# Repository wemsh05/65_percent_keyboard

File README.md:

# My first Keyboard design

This 65% keyboard is the first time I designed a pcb of my own and safe to say that I am really proud of it. The reason that I started with a keyboard is that my first mechanical keyboard used the classic ANSI layout. While usable, an idea popped in my head: what if I make my own keyboard that has 4 keys to the left of the space bar just like the laptop keyboards, and here I am.  

---

# Project Overview

This project is a two-layer FR4 board with hot-swappable cherry MX keys realized with kalih's hot swap sockets. It features an on-board usb c 2.0 port with ESD. Its MCU is the ATMega32U4 and it features an AVR 6-pin ISP connector to program the MCU firmware. The board also has a reset button and copper-grounded mounting holes. 

This project is inspired by MasterZen's 65% keyboard tutorial. But there are major differences as I did not simply copy his design. First, his designed utilized soldered ALPS footprints that in my opinion has more space for the routing and therefore slightly easier to route. The kalih hot swap sockets caused a barrier that traces can't be wired through the sockets unlike the tutorial and that took some time to get used to. Since this is my first time doing this, I also have not mastered the art of routing so the vias are probably more than the same project done by someone more skilled. 

---

# Schematic

The following is the overall keyboard schematic, which doesn't deviate too much from the tutorial. Although it seems that power flags have changed from the older kicad version the tutorial was using to kicad 10. 

The ESD protection device that I have on here is the PRTR5V0U2X, a device suitable for doing ESD protection for USB 2.0 devices. This was chosen because of ease of use and that it has a small package size. 

The AVR 6-pin ISP pin is added to flash the initial usb bootloader for future firmware uploads, it also provides a backup to not fully rely on the usb port for firmware uploads as bad firmware could render it useless. 

The grounded mounting hole pads are there because initially my plan is to eventually make an aluminum enclosure for it and these copper mounting hole pads could help with grounding. But in the event of a plastic or resin enclosure, the board would still not be in danger because of its existing grounding and ESD protection. 

---

# PCB layout

My first layout finished with a lot of vias, a lot of which isn't really necessary on the hotswap pads themselves. But I would say that there are definitely more vias than I would like on the MCU pads and near the MCU. 

Regarding the grounding, my friend who does pcbs much more than me says that usually he fills both sides that have no traces with copper but Masterzen said that I don't need to cover both sides with copper as ground as that could amplify cross-talk. He mentioned that 4 layer boards and above have their dedicated ground layers so it wouldn't be an issue for them. 

---

# Silkscreen and 3D effects

Currently, the silkscreen remains a free-hand drawing of what I imagine the final prototype to be as I don't have time to improve it. 

But on the front of 3d effects, I did end up choosing red as the final board color since I wanted the color to stand out a bit more but the official purple color is too muted. 

---

# Manufactured pictures

(Update on 8/19/2026)
The keyboard is now fully manufactured and I did have to end up choosing a matte light black since the manufacturer didn't have purple. But it did also turn out that the color was nice. For my first ever pcb project, the overall size definitely had the potential for optimization, but I believe overall this was a successful project. 

The front side 

The back side

---

# Firmware download success

I had to write the key matrix firmware for this board. Fortunately, the bootloader was already in the MCU which I somehow thought it wasn't. Currently I don't have the keys themselves to test multi-key rollover, but single keys do work:

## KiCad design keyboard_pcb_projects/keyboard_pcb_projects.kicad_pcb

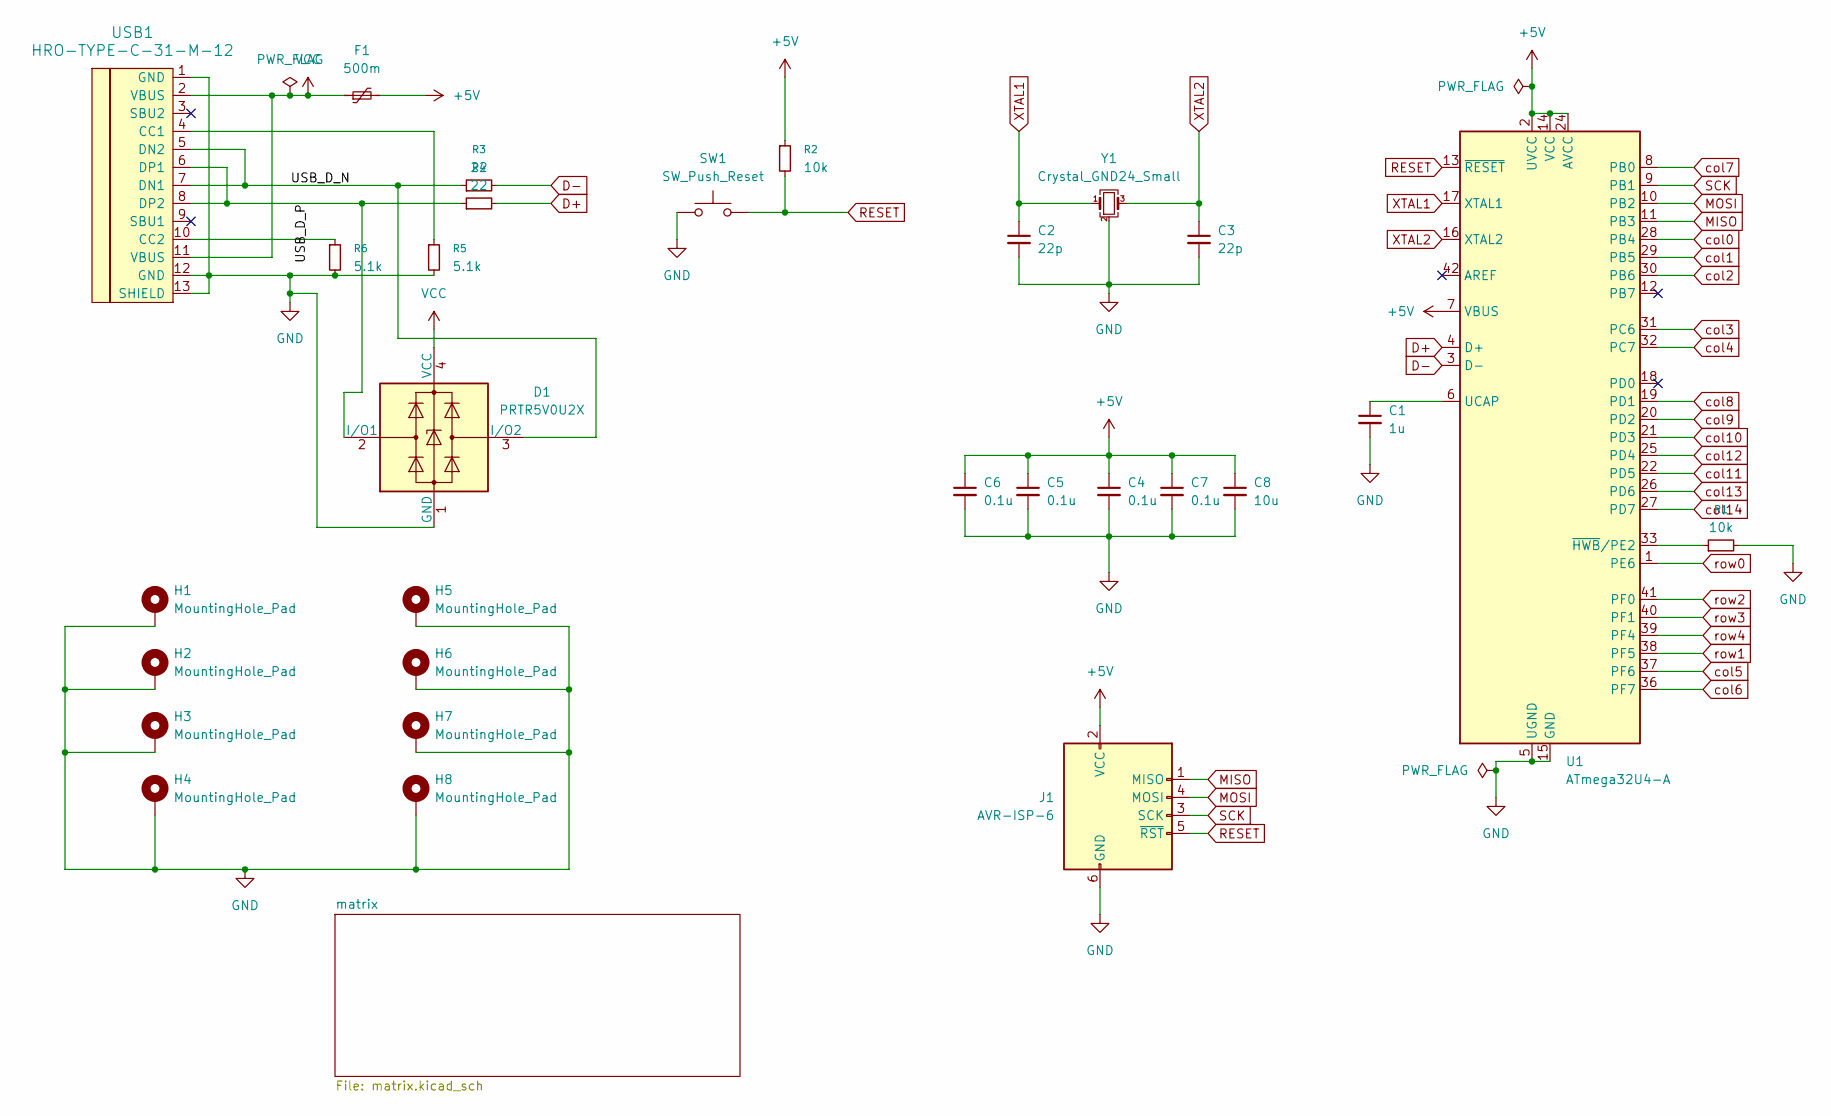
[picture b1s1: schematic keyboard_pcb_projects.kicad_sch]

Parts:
C1: 1u; C_0805_2012Metric_Pad1.18x1.45mm_HandSolder
C2, C3: 22p; C_0805_2012Metric_Pad1.18x1.45mm_HandSolder
C4, C5, C6, C7: 0.1u; C_0805_2012Metric_Pad1.18x1.45mm_HandSolder
C8: 10u; C_0805_2012Metric_Pad1.18x1.45mm_HandSolder
D1: PRTR5V0U2X; SOT-143
F1: 500m; Fuse_1206_3216Metric_Pad1.42x1.75mm_HandSolder
H1, H2, H3, H4, H5, H6, H7, H8: MountingHole_Pad; MountingHole_2.2mm_M2_Pad
J1: AVR-ISP-6; PinHeader_2x03_P2.54mm_Vertical
R1, R2: 10k; R_0805_2012Metric_Pad1.20x1.40mm_HandSolder
R3, R4: 22; R_0805_2012Metric_Pad1.20x1.40mm_HandSolder
R5, R6: 5.1k; R_0805_2012Metric_Pad1.20x1.40mm_HandSolder
SW1: SW_Push_Reset; SW_SPST_SKQG_WithStem
U1: ATmega32U4-A; TQFP-44_10x10mm_P0.8mm
USB1: HRO-TYPE-C-31-M-12; HRO-TYPE-C-31-M-12-HandSoldering
Y1: Crystal_GND24_Small; Crystal_SMD_3225-4Pin_3.2x2.5mm_HandSoldering

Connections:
+5V: C4.1, C5.1, C6.1, C7.1, C8.1, F1.2, J1.2 (VCC), R2.1, U1.2 (UVCC), U1.7 (VBUS), U1.14 (VCC), U1.24 (AVCC), U1.34 (VCC), U1.44 (AVCC)
/USB_D_N: D1.3 (I/O2), R3.1, USB1.5 (DN2), USB1.7 (DN1)
/USB_D_P: D1.2 (I/O1), R4.1, USB1.6 (DP1), USB1.8 (DP2)
D+: R4.2, U1.4 (D+)
D-: R3.2, U1.3 (D-)
GND: C1.2, C2.2, C3.2, C4.2, C5.2, C6.2, C7.2, C8.2, D1.1 (GND), H1.1 (1_1), H2.1 (1_1), H3.1 (1_1), H4.1 (1_1), H5.1 (1_1), H6.1 (1_1), H7.1 (1_1), H8.1 (1_1), J1.6 (GND), R1.2, R5.2, R6.2, SW1.1, U1.5 (UGND), U1.15 (GND), U1.23 (GND), U1.35 (GND), U1.43 (GND), USB1.1 (GND), USB1.12 (GND), USB1.13 (SHIELD), Y1.2 (G), Y1.4 (G)
MISO: J1.1 (MISO), U1.11 (PB3)
MOSI: J1.4 (MOSI), U1.10 (PB2)
unnamed: C1.1, U1.6 (UCAP)
unnamed: R1.1, U1.33 (~HWB/PE2)
unnamed: R5.1, USB1.4 (CC1)
unnamed: R6.1, USB1.10 (CC2)
RESET: J1.5 (~RST), R2.2, SW1.2, U1.13 (~RESET)
SCK: J1.3 (SCK), U1.9 (PB1)
VCC: D1.4 (VCC), F1.1, USB1.2 (VBUS), USB1.11 (VBUS)
XTAL1: C2.1, U1.17 (XTAL1), Y1.1
XTAL2: C3.1, U1.16 (XTAL2), Y1.3
col0: U1.28 (PB4); also elsewhere on the board
col1: U1.29 (PB5); also elsewhere on the board
col2: U1.30 (PB6); also elsewhere on the board
col3: U1.31 (PC6); also elsewhere on the board
col4: U1.32 (PC7); also elsewhere on the board
col5: U1.37 (PF6); also elsewhere on the board
col6: U1.36 (PF7); also elsewhere on the board
col7: U1.8 (PB0); also elsewhere on the board
col8: U1.19 (PD1); also elsewhere on the board
col9: U1.20 (PD2); also elsewhere on the board
col10: U1.21 (PD3); also elsewhere on the board
col11: U1.22 (PD5); also elsewhere on the board
col12: U1.25 (PD4); also elsewhere on the board
col13: U1.26 (PD6); also elsewhere on the board
col14: U1.27 (PD7); also elsewhere on the board
row0: U1.1 (PE6); also elsewhere on the board
row1: U1.38 (PF5); also elsewhere on the board
row2: U1.41 (PF0); also elsewhere on the board
row3: U1.40 (PF1); also elsewhere on the board
row4: U1.39 (PF4); also elsewhere on the board

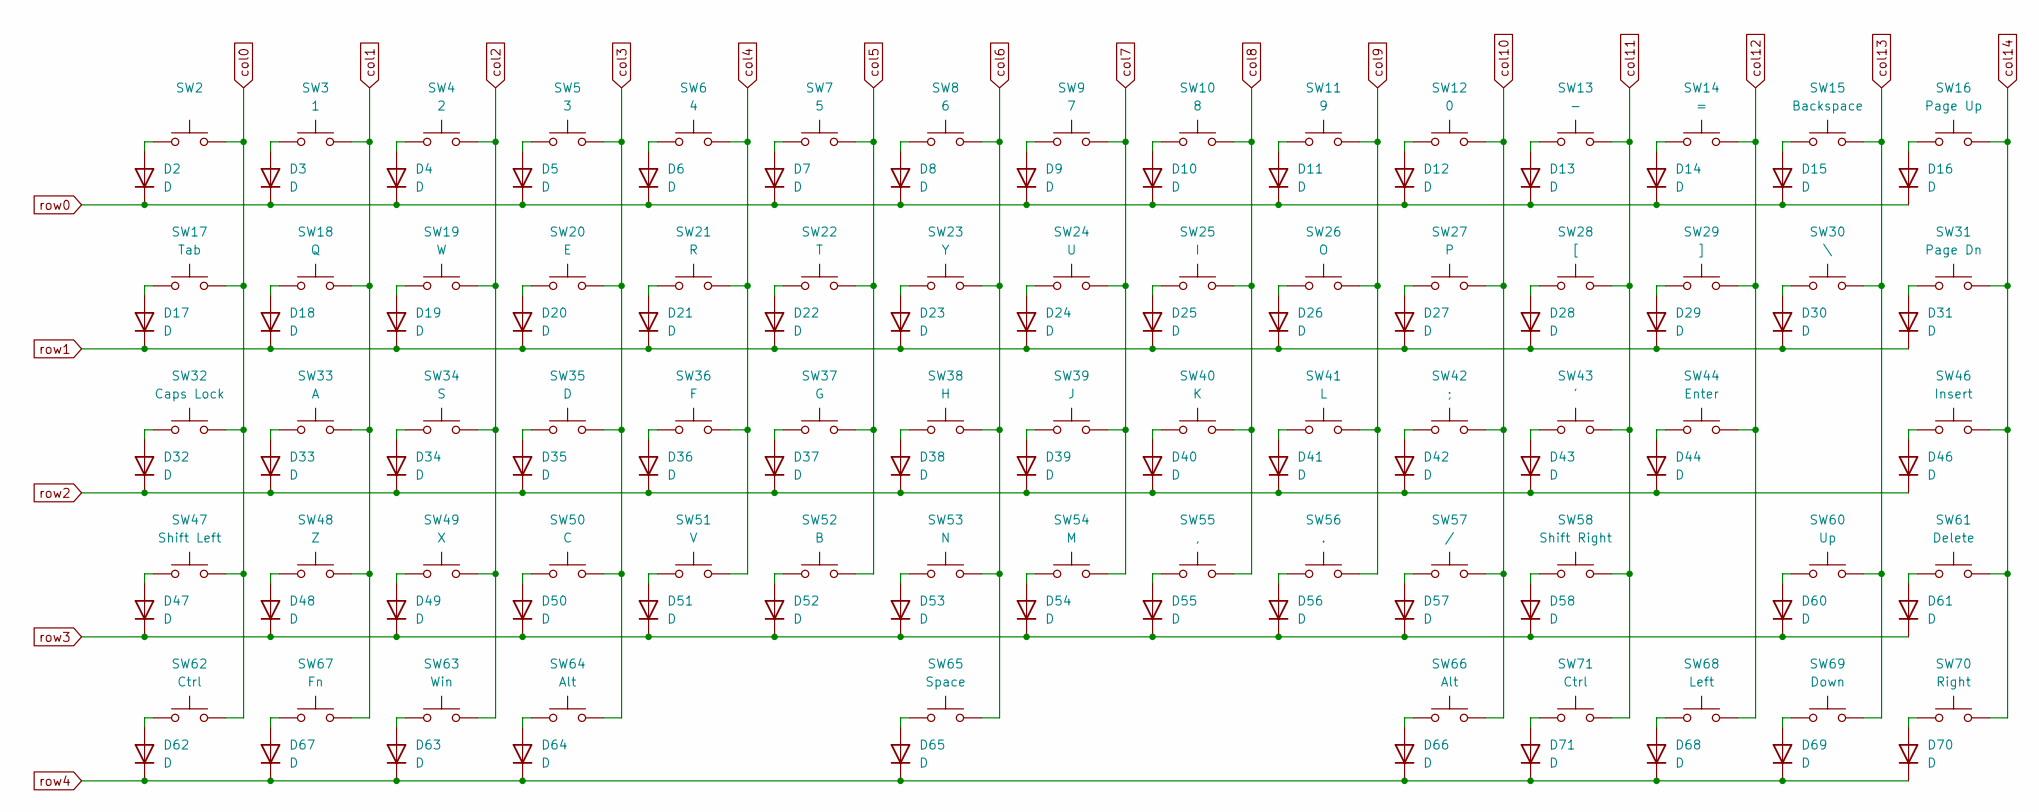
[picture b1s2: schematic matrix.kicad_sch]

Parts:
D2, D3, D4, D5, D6, D7, D8, D9, D10, D11, D12, D13, D14, D15, D16, D17, D18, D19, D20, D21, D22, D23, D24, D25, D26, D27, D28, D29, D30, D31, D32, D33, D34, D35, D36, D37, D38, D39, D40, D41, D42, D43, D44, D46, D47, D48, D49, D50, D51, D52, D53, D54, D55, D56, D57, D58, D60, D61, D62, D63, D64, D65, D66, D67, D68, D69, D70, D71: D; D_SOD-123
SW2: MX-Hotswap-1U
SW3: 1; MX-Hotswap-1U
SW4: 2; MX-Hotswap-1U
SW5: 3; MX-Hotswap-1U
SW6: 4; MX-Hotswap-1U
SW7: 5; MX-Hotswap-1U
SW8: 6; MX-Hotswap-1U
SW9: 7; MX-Hotswap-1U
SW10: 8; MX-Hotswap-1U
SW11: 9; MX-Hotswap-1U
SW12: 0; MX-Hotswap-1U
SW13: -; MX-Hotswap-1U
SW14: =; MX-Hotswap-1U
SW15: Backspace; MX-Hotswap-2U
SW16: Page Up; MX-Hotswap-1U
SW17: Tab; MX-Hotswap-1.5U
SW18: Q; MX-Hotswap-1U
SW19: W; MX-Hotswap-1U
SW20: E; MX-Hotswap-1U
SW21: R; MX-Hotswap-1U
SW22: T; MX-Hotswap-1U
SW23: Y; MX-Hotswap-1U
SW24: U; MX-Hotswap-1U
SW25: I; MX-Hotswap-1U
SW26: O; MX-Hotswap-1U
SW27: P; MX-Hotswap-1U
SW28: [; MX-Hotswap-1U
SW29: ]; MX-Hotswap-1U
SW30: \; MX-Hotswap-1.5U
SW31: Page Dn; MX-Hotswap-1U
SW32: Caps Lock; MX-Hotswap-1.75U
SW33: A; MX-Hotswap-1U
SW34: S; MX-Hotswap-1U
SW35: D; MX-Hotswap-1U
SW36: F; MX-Hotswap-1U
SW37: G; MX-Hotswap-1U
SW38: H; MX-Hotswap-1U
SW39: J; MX-Hotswap-1U
SW40: K; MX-Hotswap-1U
SW41: L; MX-Hotswap-1U
SW42: ;; MX-Hotswap-1U
SW43: '; MX-Hotswap-1U
SW44: Enter; MX-Hotswap-2.25U
SW46: Insert; MX-Hotswap-1U
SW47: Shift Left; MX-Hotswap-2.25U
SW48: Z; MX-Hotswap-1U
SW49: X; MX-Hotswap-1U
SW50: C; MX-Hotswap-1U
SW51: V; MX-Hotswap-1U
SW52: B; MX-Hotswap-1U
SW53: N; MX-Hotswap-1U
SW54: M; MX-Hotswap-1U
SW55: ,; MX-Hotswap-1U
SW56: .; MX-Hotswap-1U
SW57: /; MX-Hotswap-1U
SW58: Shift Right; MX-Hotswap-1.75U
SW60: Up; MX-Hotswap-1U
SW61: Delete; MX-Hotswap-1U
SW62: Ctrl; MX-Hotswap-1.25U
SW63: Win; MX-Hotswap-1.25U
SW64: Alt; MX-Hotswap-1.25U
SW65: Space; MX-Hotswap-6.25U
SW66: Alt; MX-Hotswap-1U
SW67: Fn; MX-Hotswap-1U
SW68: Left; MX-Hotswap-1U
SW69: Down; MX-Hotswap-1U
SW70: Right; MX-Hotswap-1U
SW71: Ctrl; MX-Hotswap-1U

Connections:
unnamed: D2.2 (A), SW2.1
unnamed: D3.2 (A), SW3.1
unnamed: D4.2 (A), SW4.1
unnamed: D5.2 (A), SW5.1
unnamed: D6.2 (A), SW6.1
unnamed: D7.2 (A), SW7.1
unnamed: D8.2 (A), SW8.1
unnamed: D9.2 (A), SW9.1
unnamed: D10.2 (A), SW10.1
unnamed: D11.2 (A), SW11.1
unnamed: D12.2 (A), SW12.1
unnamed: D13.2 (A), SW13.1
unnamed: D14.2 (A), SW14.1
unnamed: D15.2 (A), SW15.1
unnamed: D16.2 (A), SW16.1
unnamed: D17.2 (A), SW17.1
unnamed: D18.2 (A), SW18.1
unnamed: D19.2 (A), SW19.1
unnamed: D20.2 (A), SW20.1
unnamed: D21.2 (A), SW21.1
unnamed: D22.2 (A), SW22.1
unnamed: D23.2 (A), SW23.1
unnamed: D24.2 (A), SW24.1
unnamed: D25.2 (A), SW25.1
unnamed: D26.2 (A), SW26.1
unnamed: D27.2 (A), SW27.1
unnamed: D28.2 (A), SW28.1
unnamed: D29.2 (A), SW29.1
unnamed: D30.2 (A), SW30.1
unnamed: D31.2 (A), SW31.1
unnamed: D32.2 (A), SW32.1
unnamed: D33.2 (A), SW33.1
unnamed: D34.2 (A), SW34.1
unnamed: D35.2 (A), SW35.1
unnamed: D36.2 (A), SW36.1
unnamed: D37.2 (A), SW37.1
unnamed: D38.2 (A), SW38.1
unnamed: D39.2 (A), SW39.1
unnamed: D40.2 (A), SW40.1
unnamed: D41.2 (A), SW41.1
unnamed: D42.2 (A), SW42.1
unnamed: D43.2 (A), SW43.1
unnamed: D44.2 (A), SW44.1
unnamed: D46.2 (A), SW46.1
unnamed: D47.2 (A), SW47.1
unnamed: D48.2 (A), SW48.1
unnamed: D49.2 (A), SW49.1
unnamed: D50.2 (A), SW50.1
unnamed: D51.2 (A), SW51.1
unnamed: D52.2 (A), SW52.1
unnamed: D53.2 (A), SW53.1
unnamed: D54.2 (A), SW54.1
unnamed: D55.2 (A), SW55.1
unnamed: D56.2 (A), SW56.1
unnamed: D57.2 (A), SW57.1
unnamed: D58.2 (A), SW58.1
unnamed: D60.2 (A), SW60.1
unnamed: D61.2 (A), SW61.1
unnamed: D62.2 (A), SW62.1
unnamed: D63.2 (A), SW63.1
unnamed: D64.2 (A), SW64.1
unnamed: D65.2 (A), SW65.1
unnamed: D66.2 (A), SW66.1
unnamed: D67.2 (A), SW67.1
unnamed: D68.2 (A), SW68.1
unnamed: D69.2 (A), SW69.1
unnamed: D70.2 (A), SW70.1
unnamed: D71.2 (A), SW71.1
col0: SW2.2, SW17.2, SW32.2, SW47.2, SW62.2; also elsewhere on the board
col1: SW3.2, SW18.2, SW33.2, SW48.2, SW67.2; also elsewhere on the board
col2: SW4.2, SW19.2, SW34.2, SW49.2, SW63.2; also elsewhere on the board
col3: SW5.2, SW20.2, SW35.2, SW50.2, SW64.2; also elsewhere on the board
col4: SW6.2, SW21.2, SW36.2, SW51.2; also elsewhere on the board
col5: SW7.2, SW22.2, SW37.2, SW52.2; also elsewhere on the board
col6: SW8.2, SW23.2, SW38.2, SW53.2, SW65.2; also elsewhere on the board
col7: SW9.2, SW24.2, SW39.2, SW54.2; also elsewhere on the board
col8: SW10.2, SW25.2, SW40.2, SW55.2; also elsewhere on the board
col9: SW11.2, SW26.2, SW41.2, SW56.2; also elsewhere on the board
col10: SW12.2, SW27.2, SW42.2, SW57.2, SW66.2; also elsewhere on the board
col11: SW13.2, SW28.2, SW43.2, SW58.2, SW71.2; also elsewhere on the board
col12: SW14.2, SW29.2, SW44.2, SW68.2; also elsewhere on the board
col13: SW15.2, SW30.2, SW60.2, SW69.2; also elsewhere on the board
col14: SW16.2, SW31.2, SW46.2, SW61.2, SW70.2; also elsewhere on the board
row0: D2.1 (K), D3.1 (K), D4.1 (K), D5.1 (K), D6.1 (K), D7.1 (K), D8.1 (K), D9.1 (K), D10.1 (K), D11.1 (K), D12.1 (K), D13.1 (K), D14.1 (K), D15.1 (K), D16.1 (K); also elsewhere on the board
row1: D17.1 (K), D18.1 (K), D19.1 (K), D20.1 (K), D21.1 (K), D22.1 (K), D23.1 (K), D24.1 (K), D25.1 (K), D26.1 (K), D27.1 (K), D28.1 (K), D29.1 (K), D30.1 (K), D31.1 (K); also elsewhere on the board
row2: D32.1 (K), D33.1 (K), D34.1 (K), D35.1 (K), D36.1 (K), D37.1 (K), D38.1 (K), D39.1 (K), D40.1 (K), D41.1 (K), D42.1 (K), D43.1 (K), D44.1 (K), D46.1 (K); also elsewhere on the board
row3: D47.1 (K), D48.1 (K), D49.1 (K), D50.1 (K), D51.1 (K), D52.1 (K), D53.1 (K), D54.1 (K), D55.1 (K), D56.1 (K), D57.1 (K), D58.1 (K), D60.1 (K), D61.1 (K); also elsewhere on the board
row4: D62.1 (K), D63.1 (K), D64.1 (K), D65.1 (K), D66.1 (K), D67.1 (K), D68.1 (K), D69.1 (K), D70.1 (K), D71.1 (K); also elsewhere on the board

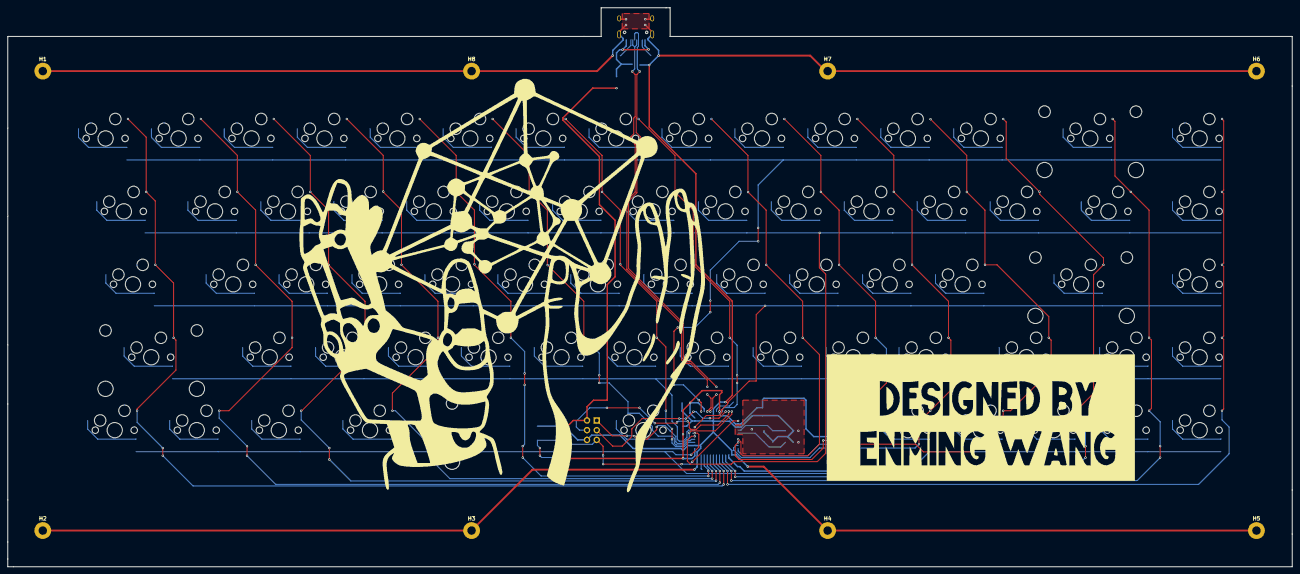
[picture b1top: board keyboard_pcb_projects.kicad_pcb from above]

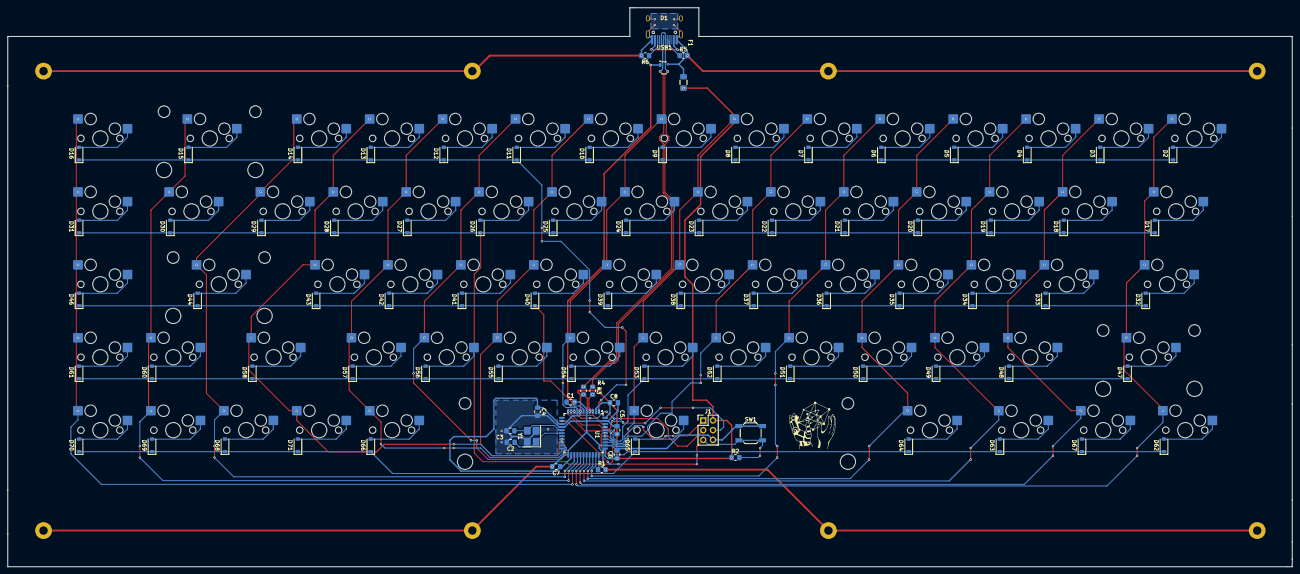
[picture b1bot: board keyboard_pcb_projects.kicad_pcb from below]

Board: 2 copper layers, 335.5 x 146.0 mm, 165 parts (157 on the bottom side), 105 nets.

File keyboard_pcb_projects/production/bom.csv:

Designator,Footprint,Quantity,Value,LCSC Part #
C1,0805,1,1u,
"C2, C3",0805,2,22p,
"C4, C5, C6, C7",0805,4,0.1u,
C8,0805,1,10u,
D1,SOT-143,1,PRTR5V0U2X,
"D10, D11, D12, D13, D14, D15, D16, D17, D18, D19, D2, D20, D21, D22, D23, D24, D25, D26, D27, D28, D29, D3, D30, D31, D32, D33, D34, D35, D36, D37, D38, D39, D4, D40, D41, D42, D43, D44, D46, D47, D48, D49, D5, D50, D51, D52, D53, D54, D55, D56, D57, D58, D6, D60, D61, D62, D63, D64, D65, D66, D67, D68, D69, D7, D70, D71, D8, D9",D_SOD-123,68,D,
F1,1206,1,500m,
J1,PinHeader_2x03_P2.54mm_Vertical,1,AVR-ISP-6,
"R1, R2",0805,2,10k,
"R3, R4",0805,2,22,
"R5, R6",0805,2,5.1k,
SW1,SW_SPST_SKQG_WithStem,1,SW_Push_Reset,
SW10,MX-Hotswap-1U,1,8,
SW11,MX-Hotswap-1U,1,9,
SW12,MX-Hotswap-1U,1,0,
SW13,MX-Hotswap-1U,1,-,
SW14,MX-Hotswap-1U,1,=,
SW15,MX-Hotswap-2U,1,Backspace,
SW16,MX-Hotswap-1U,1,Page Up,
SW17,MX-Hotswap-1.5U,1,Tab,
SW18,MX-Hotswap-1U,1,Q,
SW19,MX-Hotswap-1U,1,W,
SW2,MX-Hotswap-1U,1,~,
SW20,MX-Hotswap-1U,1,E,
SW21,MX-Hotswap-1U,1,R,
SW22,MX-Hotswap-1U,1,T,
SW23,MX-Hotswap-1U,1,Y,
SW24,MX-Hotswap-1U,1,U,
SW25,MX-Hotswap-1U,1,I,
SW26,MX-Hotswap-1U,1,O,
SW27,MX-Hotswap-1U,1,P,
SW28,MX-Hotswap-1U,1,[,
SW29,MX-Hotswap-1U,1,],
SW3,MX-Hotswap-1U,1,1,
SW30,MX-Hotswap-1.5U,1,\,
SW31,MX-Hotswap-1U,1,Page Dn,
SW32,MX-Hotswap-1.75U,1,Caps Lock,
SW33,MX-Hotswap-1U,1,A,
SW34,MX-Hotswap-1U,1,S,
SW35,MX-Hotswap-1U,1,D,
SW36,MX-Hotswap-1U,1,F,
SW37,MX-Hotswap-1U,1,G,
SW38,MX-Hotswap-1U,1,H,
SW39,MX-Hotswap-1U,1,J,
SW4,MX-Hotswap-1U,1,2,
SW40,MX-Hotswap-1U,1,K,
SW41,MX-Hotswap-1U,1,L,
SW42,MX-Hotswap-1U,1,;,
SW43,MX-Hotswap-1U,1,',
SW44,MX-Hotswap-2.25U,1,Enter,
SW46,MX-Hotswap-1U,1,Insert,
SW47,MX-Hotswap-2.25U,1,Shift Left,
SW48,MX-Hotswap-1U,1,Z,
SW49,MX-Hotswap-1U,1,X,
SW5,MX-Hotswap-1U,1,3,
SW50,MX-Hotswap-1U,1,C,
SW51,MX-Hotswap-1U,1,V,
SW52,MX-Hotswap-1U,1,B,
SW53,MX-Hotswap-1U,1,N,
SW54,MX-Hotswap-1U,1,M,
SW55,MX-Hotswap-1U,1,",",
SW56,MX-Hotswap-1U,1,.,
SW57,MX-Hotswap-1U,1,/,
SW58,MX-Hotswap-1.75U,1,Shift Right,
SW6,MX-Hotswap-1U,1,4,
SW60,MX-Hotswap-1U,1,Up,
SW61,MX-Hotswap-1U,1,Delete,
SW62,MX-Hotswap-1.25U,1,Ctrl,
SW63,MX-Hotswap-1.25U,1,Win,
SW64,MX-Hotswap-1.25U,1,Alt,
SW65,MX-Hotswap-6.25U,1,Space,
SW66,MX-Hotswap-1U,1,Alt,
SW67,MX-Hotswap-1U,1,Fn,
SW68,MX-Hotswap-1U,1,Left,
SW69,MX-Hotswap-1U,1,Down,
SW7,MX-Hotswap-1U,1,5,
SW70,MX-Hotswap-1U,1,Right,
SW71,MX-Hotswap-1U,1,Ctrl,
SW8,MX-Hotswap-1U,1,6,
SW9,MX-Hotswap-1U,1,7,
U1,TQFP-44_10x10mm_P0.8mm,1,ATmega32U4-A,
USB1,HRO-TYPE-C-31-M-12-HandSoldering,1,HRO-TYPE-C-31-M-12,
Y1,Crystal_SMD_3225-4Pin_3.2x2.5mm_HandSoldering,1,Crystal_GND24_Small,

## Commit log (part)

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2026-06-18 finally wired up two of the positive ends of the usb controller
